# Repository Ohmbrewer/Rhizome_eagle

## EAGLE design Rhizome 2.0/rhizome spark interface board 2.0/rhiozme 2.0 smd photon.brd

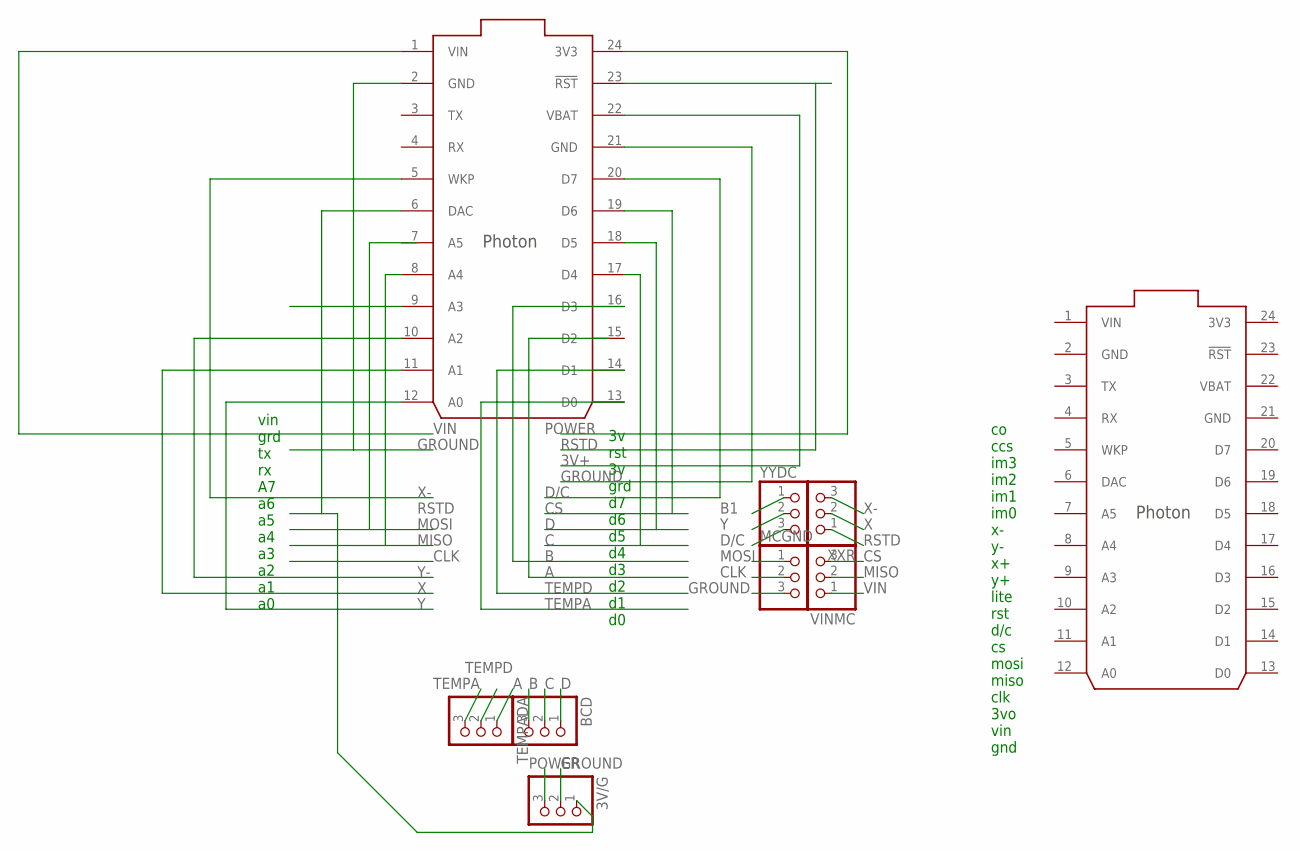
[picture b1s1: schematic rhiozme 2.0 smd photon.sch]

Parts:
3V/G: PINHD-1X3CB; 1X03-CLEANBIG
BCD: PINHD-1X3CB; 1X03-CLEANBIG
MCGND: PINHD-1X3CB; 1X03-CLEANBIG
TEMPADA: PINHD-1X3CB; 1X03-CLEANBIG
U$2: PHOTON_SMD
U$3: PHOTON_WITH_HEADERS; PHOTON
VINMC: PINHD-1X3CB; 1X03-CLEANBIG
XXR: PINHD-1X3CB; 1X03-CLEANBIG
YYDC: PINHD-1X3CB; 1X03-CLEANBIG

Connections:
3V3: U$3.24 (3V3)
3V+: U$2.22 (VBAT)
A: TEMPADA.1
B: BCD.3, U$2.16 (D3)
B1: YYDC.1
C: BCD.2, U$2.17 (D4)
CLK: MCGND.2
CS: U$2.19 (D6), VINMC.3
D: BCD.1, U$2.18 (D5)
D/C: U$2.20 (D7), YYDC.3
GND: U$3.2 (GND), U$3.21 (GND)
GROUND: 3V/G.2, MCGND.3, U$2.2 (GND), U$2.21 (GND)
MISO: U$2.8 (A4), VINMC.2
MOSI: MCGND.1
unnamed: 3V/G.1, U$2.6 (DAC)
POWER: 3V/G.3, U$2.24 (3V3)
RSTD: U$2.23 (!RST), XXR.1
TEMPA: TEMPADA.3, U$2.13 (D0)
TEMPD: TEMPADA.2, U$2.14 (D1)
VBAT: U$3.22 (VBAT)
VIN: U$2.1 (VIN), U$3.1 (VIN), VINMC.1
X: U$2.11 (A1), XXR.2
X-: U$2.5 (WKP), XXR.3
Y: U$2.12 (A0), YYDC.2
Y-: U$2.10 (A2)

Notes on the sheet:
vin grd tx rx A7 a6 a5 a4 a3 a2 a1 a0
3v rst 3v grd d7 d6 d5 d4 d3 d2 d1 d0
co ccs im3 im2 im1 im0 x- y- x+ y+ lite rst d/c cs mosi miso clk 3vo vin gnd

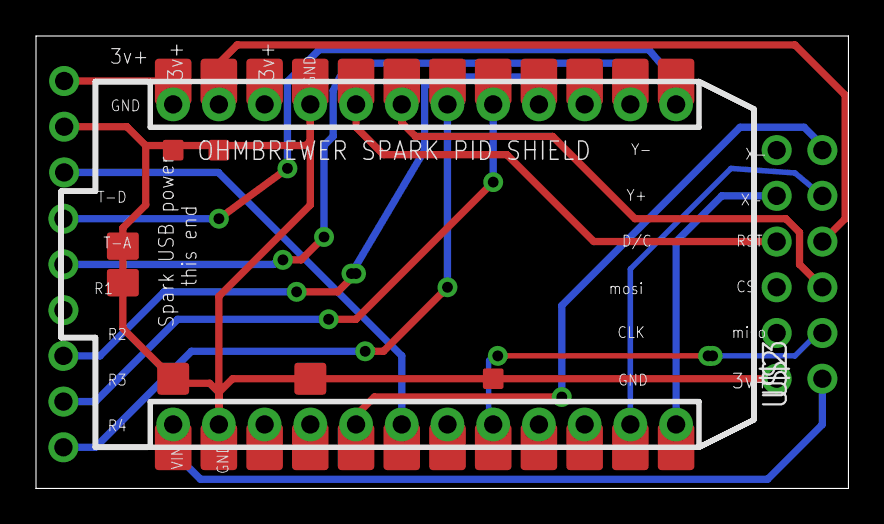
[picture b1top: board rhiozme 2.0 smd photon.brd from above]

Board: 2 copper layers, 45.1 x 25.1 mm, 10 parts (0 on the bottom side), 17 nets.

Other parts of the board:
U$1: STAND-OFF-TIGHT

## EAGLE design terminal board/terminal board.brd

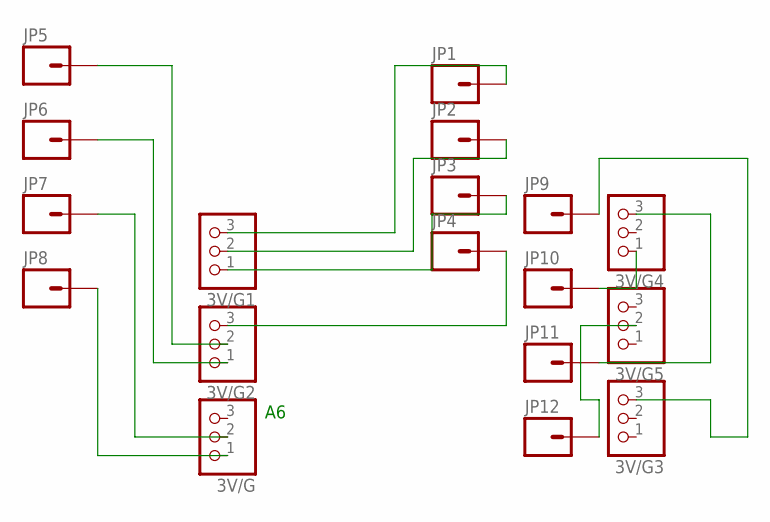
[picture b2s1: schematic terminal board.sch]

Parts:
3V/G, 3V/G1, 3V/G2, 3V/G3, 3V/G4, 3V/G5: PINHD-1X3CB; 1X03-CLEANBIG
JP1, JP2, JP3, JP4, JP5, JP6, JP7, JP8, JP9, JP10, JP11, JP12: M01PTH_2MM; 1X01_2MM

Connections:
unnamed: 3V/G2.2, JP5.1
unnamed: 3V/G2.1, JP6.1
unnamed: 3V/G.2, JP7.1
unnamed: 3V/G.1, JP8.1
unnamed: 3V/G1.3, JP1.1
unnamed: 3V/G1.2, JP2.1
unnamed: 3V/G1.1, JP3.1
unnamed: 3V/G2.3, JP4.1
unnamed: 3V/G4.1, JP10.1
unnamed: 3V/G4.3, JP11.1
unnamed: 3V/G5.2, JP12.1
unnamed: 3V/G3.3, JP9.1

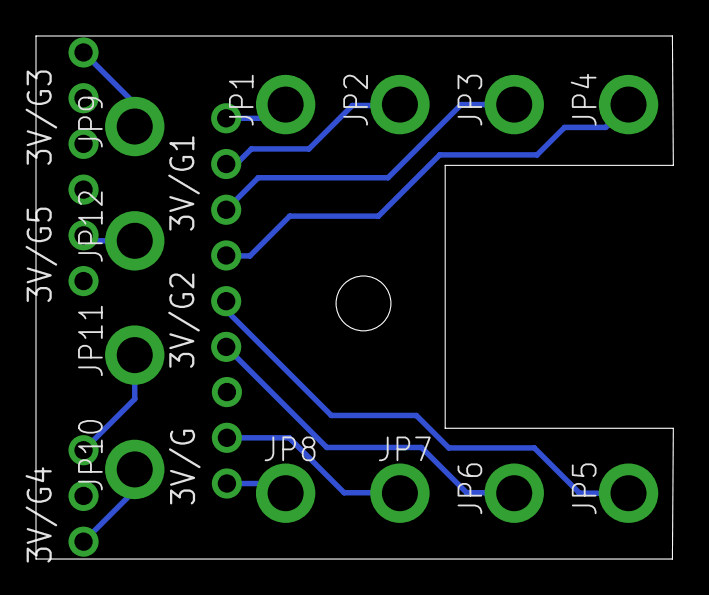
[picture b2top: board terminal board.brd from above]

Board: 2 copper layers, 35.4 x 29.1 mm, 19 parts (0 on the bottom side), 12 nets.

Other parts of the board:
U$1: STAND-OFF-TIGHT

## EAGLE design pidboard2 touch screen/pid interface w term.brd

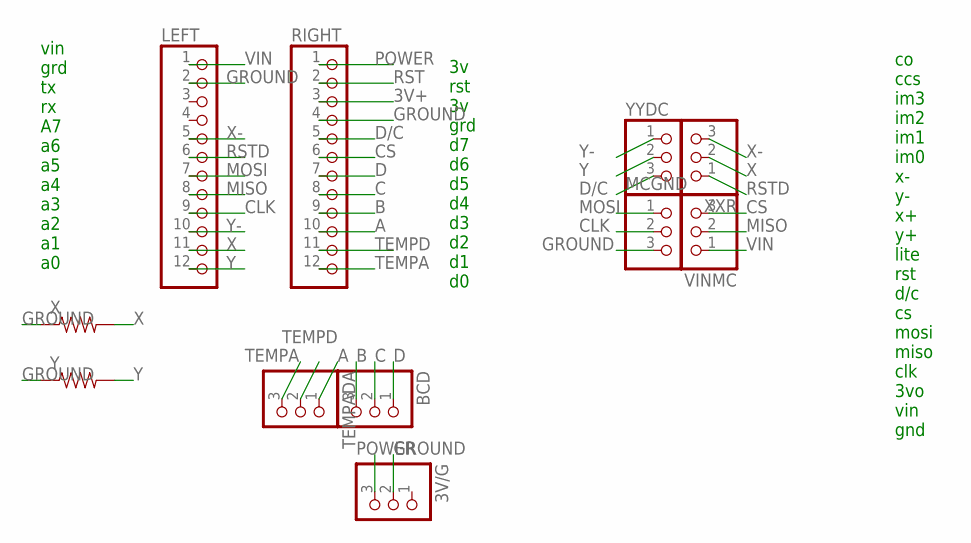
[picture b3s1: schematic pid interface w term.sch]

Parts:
3V/G: PINHD-1X3CB; 1X03-CLEANBIG
BCD: PINHD-1X3CB; 1X03-CLEANBIG
LEFT: PINHD-1X12-CB; 1X12-CB
MCGND: PINHD-1X3CB; 1X03-CLEANBIG
RIGHT: PINHD-1X12-CB; 1X12-CB
TEMPADA: PINHD-1X3CB; 1X03-CLEANBIG
VINMC: PINHD-1X3CB; 1X03-CLEANBIG
X: 10KOHM-1/6W-5%(PTH)KIT; AXIAL-0.3-KIT
XXR: PINHD-1X3CB; 1X03-CLEANBIG
Y: 10KOHM-1/6W-5%(PTH)KIT; AXIAL-0.3-KIT
YYDC: PINHD-1X3CB; 1X03-CLEANBIG

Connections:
3V+: RIGHT.3
A: RIGHT.10, TEMPADA.1
B: BCD.3, RIGHT.9
C: BCD.2, RIGHT.8
CLK: LEFT.9, MCGND.2
CS: RIGHT.6, VINMC.3
D: BCD.1, RIGHT.7
D/C: RIGHT.5, YYDC.3
GROUND: 3V/G.2, LEFT.2, MCGND.3, RIGHT.4, X.P$1 (1), Y.P$1 (1)
MISO: LEFT.8, VINMC.2
MOSI: LEFT.7, MCGND.1
POWER: 3V/G.3, RIGHT.1
RST: RIGHT.2
RSTD: LEFT.6, XXR.1
TEMPA: RIGHT.12, TEMPADA.3
TEMPD: RIGHT.11, TEMPADA.2
VIN: LEFT.1, VINMC.1
X: LEFT.11, X.P$2 (2), XXR.2
X-: LEFT.5, XXR.3
Y: LEFT.12, Y.P$2 (2), YYDC.2
Y-: LEFT.10, YYDC.1

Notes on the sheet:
vin grd tx rx A7 a6 a5 a4 a3 a2 a1 a0
3v rst 3v grd d7 d6 d5 d4 d3 d2 d1 d0
co ccs im3 im2 im1 im0 x- y- x+ y+ lite rst d/c cs mosi miso clk 3vo vin gnd

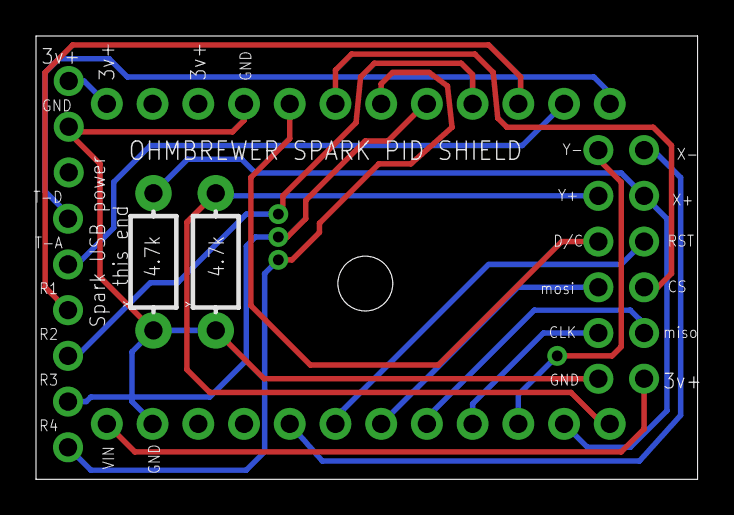
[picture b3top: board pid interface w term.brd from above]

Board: 2 copper layers, 36.8 x 24.6 mm, 12 parts (0 on the bottom side), 19 nets.

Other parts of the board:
U$1: STAND-OFF-TIGHT

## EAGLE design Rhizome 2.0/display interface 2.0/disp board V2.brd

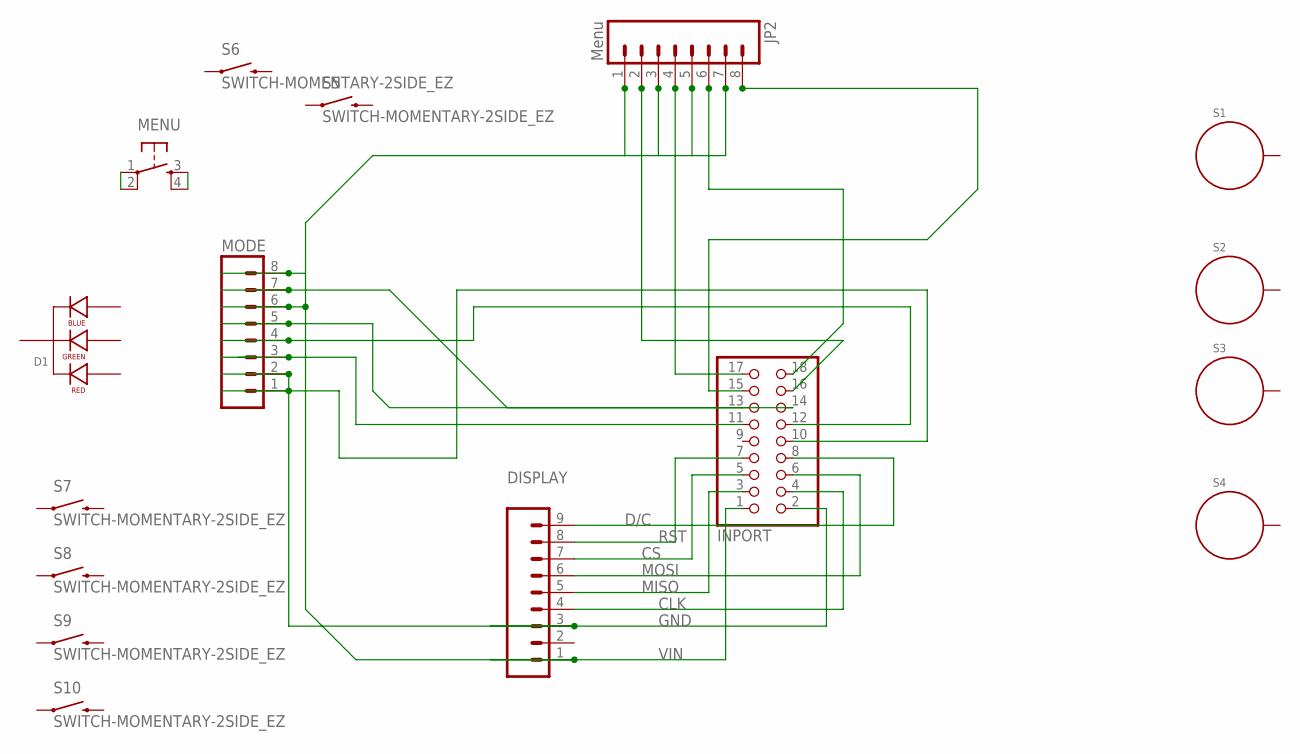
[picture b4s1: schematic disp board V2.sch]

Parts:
D1: LED-RGB-CC-THRUCLEAR; LED-RGB-THRU
DISPLAY: M09; 1X09
INPORT: PINHD-2X9-BIG; 2X09-BIG
JP2: Menu; 1X08_ROUND
MENU: TAC_SWITCHPTH; TACTILE-PTH
MODE: M08; 1X08_ROUND
S1, S2, S3, S4: STANDOFF_ELECTRICAL; STANDOFF-ELECTRICAL
S5, S6, S7, S8, S9, S10: SWITCH-MOMENTARY-2SIDE_EZ; TACTILE-PTH-SIDEEZ

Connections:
CLK: DISPLAY.4, INPORT.4
CS: DISPLAY.7, INPORT.5
D/C: DISPLAY.9, INPORT.8
GND: DISPLAY.3, INPORT.2, MODE.2
MISO: DISPLAY.5, INPORT.3
MOSI: DISPLAY.6, INPORT.6
unnamed: INPORT.17, JP2.4
unnamed: INPORT.16, JP2.2
unnamed: MENU.1, MENU.2
unnamed: INPORT.11, MODE.3
unnamed: INPORT.13, MODE.5
unnamed: INPORT.14, MODE.7
unnamed: INPORT.12, MODE.4
unnamed: INPORT.10, MODE.1
unnamed: INPORT.18, JP2.6
unnamed: INPORT.15, JP2.8
unnamed: MENU.3, MENU.4
RST: DISPLAY.8, INPORT.7
VIN: DISPLAY.1, INPORT.1, JP2.1, JP2.3, JP2.5, JP2.7, MODE.6, MODE.8

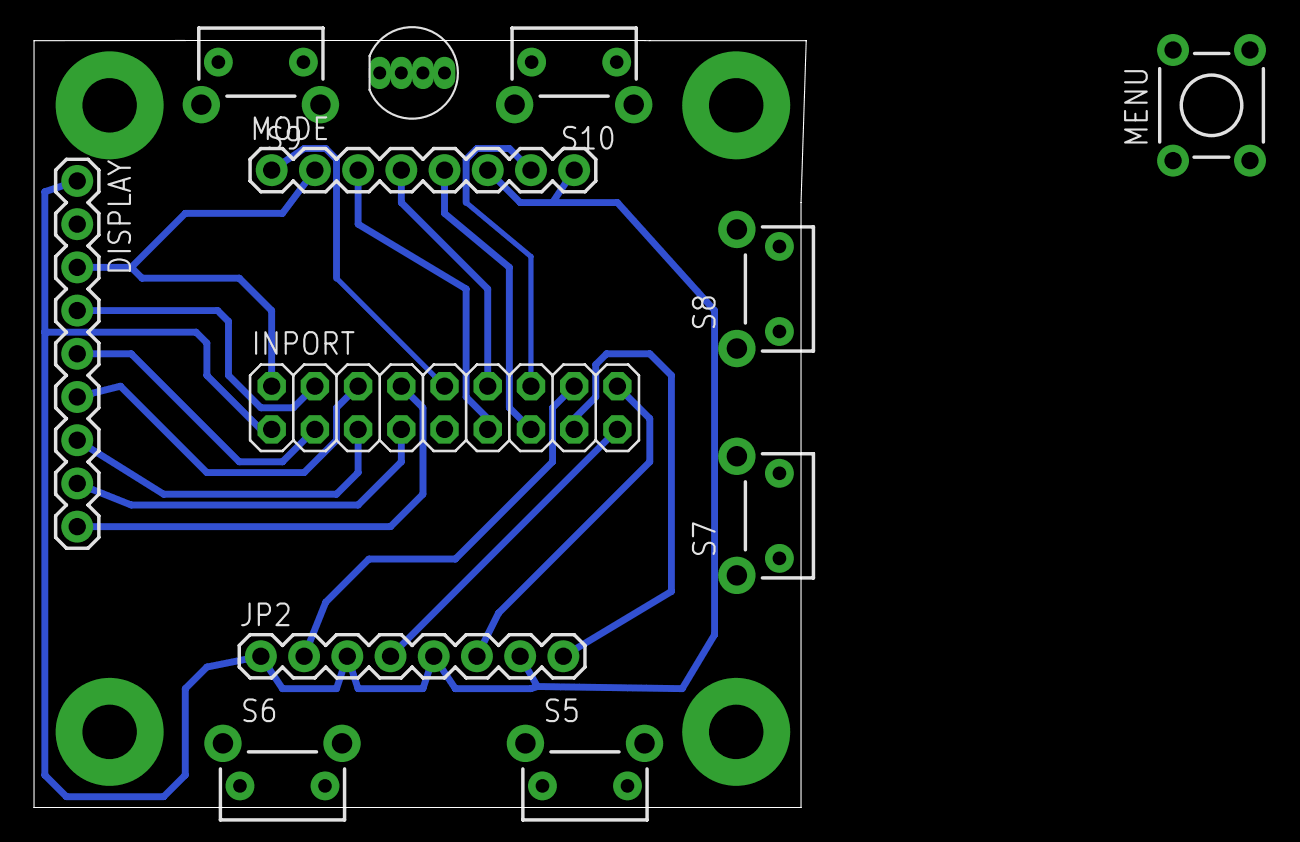
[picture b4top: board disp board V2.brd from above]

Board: 2 copper layers, 45.4 x 45.1 mm, 16 parts (0 on the bottom side), 19 nets.

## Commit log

2017-11-18 adds all existing files and new V2 rhizome boards

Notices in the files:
parts and their libraries:
SparkFun-LED: Licensing: Creative Commons ShareAlike 4.0 International - https://creativecommons.org/licenses/by-sa/4.0
